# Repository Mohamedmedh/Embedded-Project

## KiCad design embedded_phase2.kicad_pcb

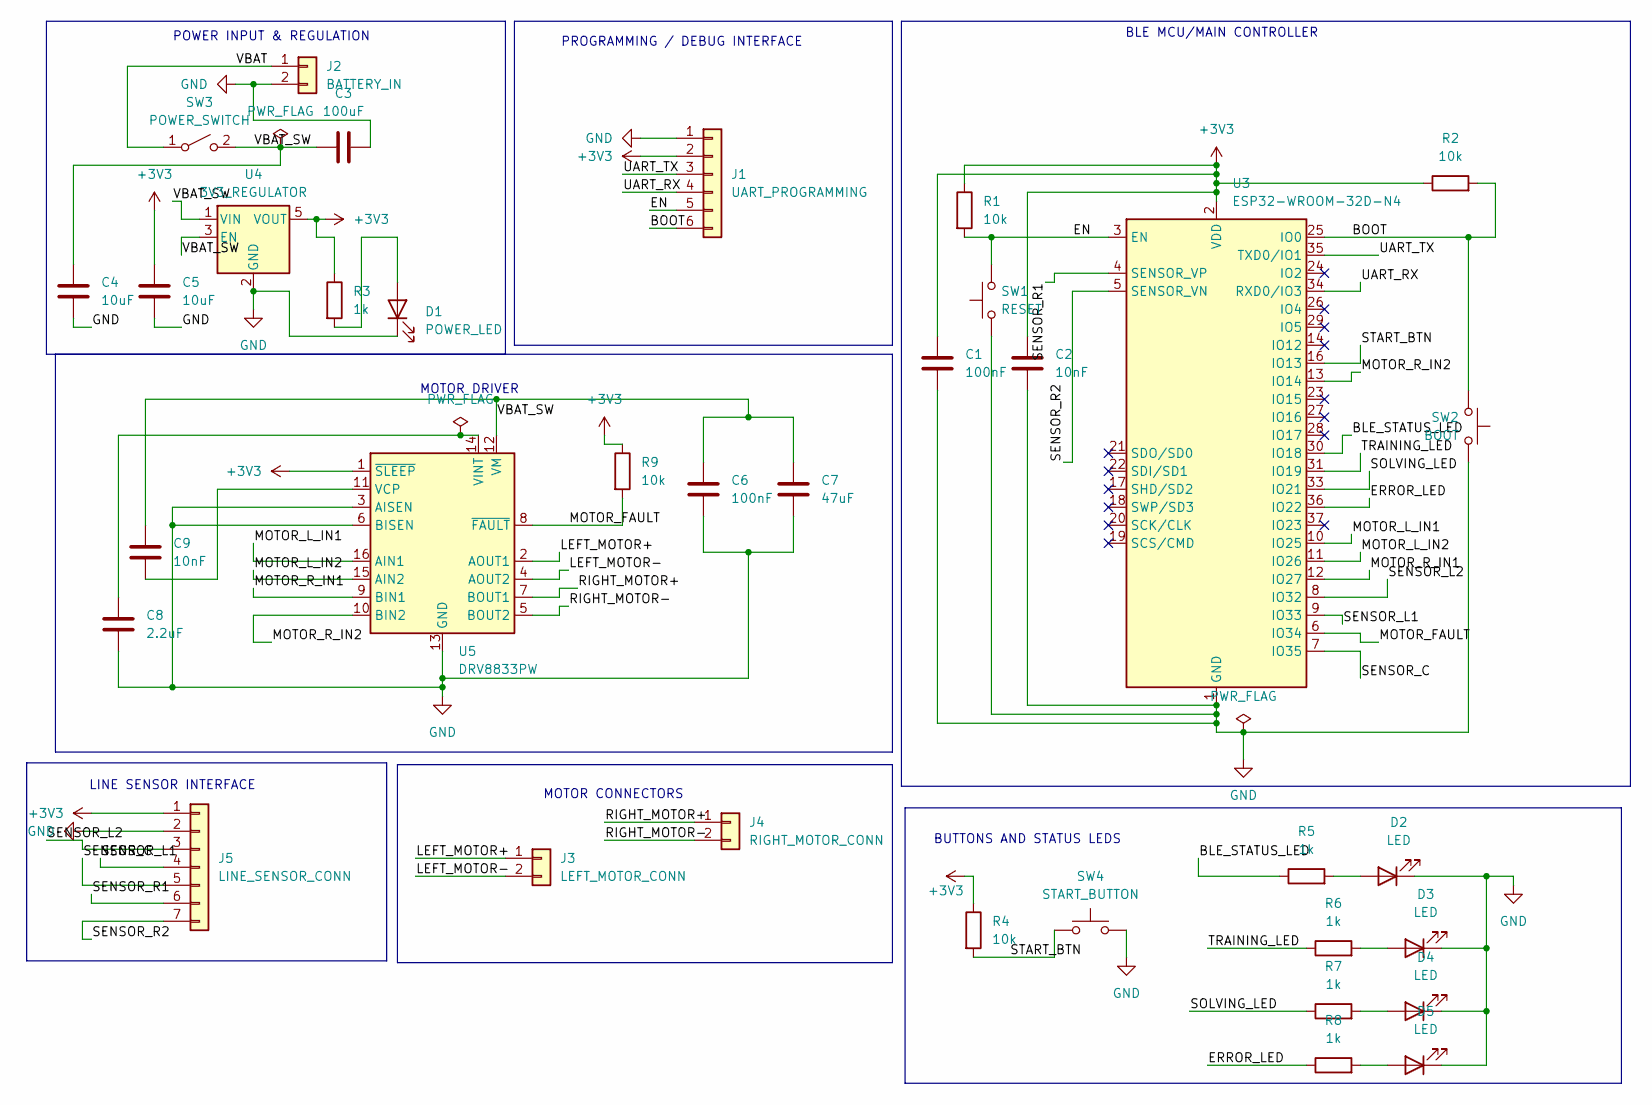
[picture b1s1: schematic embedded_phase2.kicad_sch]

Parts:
C1, C6: 100nF; C_0805_2012Metric
C2, C9: 10nF; C_0805_2012Metric
C3: 100uF; C_1206_3216Metric
C4, C5: 10uF; C_0805_2012Metric
C7: 47uF; C_1206_3216Metric
C8: 2.2uF; C_0805_2012Metric
D1: POWER_LED; LED_0805_2012Metric
D2, D3, D4, D5: LED; LED_0805_2012Metric
J1: UART_PROGRAMMING; PinHeader_1x06_P2.54mm_Vertical_SMD_Pin1Left
J2: BATTERY_IN; PinHeader_1x02_P2.54mm_Vertical_SMD_Pin1Left
J3: LEFT_MOTOR_CONN; PinHeader_1x02_P2.54mm_Vertical_SMD_Pin1Left
J4: RIGHT_MOTOR_CONN; PinHeader_1x02_P2.54mm_Vertical_SMD_Pin1Left
J5: LINE_SENSOR_CONN; PinHeader_1x07_P2.54mm_Vertical_SMD_Pin1Left
R1, R2, R4, R9: 10k; R_0805_2012Metric
R3, R5, R6, R7, R8: 1k; R_0805_2012Metric
SW1: RESET; SW_SPST_TL3342
SW2: BOOT; SW_SPST_TL3342
SW3: POWER_SWITCH; SW_SPST_TL3342
SW4: START_BUTTON; SW_SPST_TL3342
U3: ESP32-WROOM-32D-N4; ESP32-WROOM-32D; MPN ESP32-WR00M-32D-N4; LCSC C473012
U4: 3V3_REGULATOR; SOT-23-5
U5: DRV8833PW; TSSOP-16_4.4x5mm_P0.65mm

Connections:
+3V3: C1.1, C2.1, C5.1, J1.2, J5.1, R1.1, R2.1, R3.1, R4.1, R9.1, U3.2 (VDD), U4.5 (VOUT), U5.1 (~SLEEP)
/BLE_STATUS_LED: R5.1, U3.30 (IO18)
/BOOT: J1.6, R2.2, SW2.2, U3.25 (IO0)
/EN: J1.5, R1.2, SW1.2, U3.3 (EN)
/ERROR_LED: R8.1, U3.36 (IO22)
/LEFT_MOTOR+: J3.1, U5.2 (AOUT1)
/LEFT_MOTOR-: J3.2, U5.4 (AOUT2)
/MOTOR_FAULT: R9.2, U3.6 (IO34), U5.8 (~FAULT)
/MOTOR_L_IN1: U3.10 (IO25), U5.16 (AIN1)
/MOTOR_L_IN2: U3.11 (IO26), U5.15 (AIN2)
/MOTOR_R_IN1: U3.12 (IO27), U5.9 (BIN1)
/MOTOR_R_IN2: U3.13 (IO14), U5.10 (BIN2)
/RIGHT_MOTOR+: J4.1, U5.7 (BOUT1)
/RIGHT_MOTOR-: J4.2, U5.5 (BOUT2)
/SENSOR_C: J5.5, U3.7 (IO35)
/SENSOR_L1: J5.4, U3.9 (IO33)
/SENSOR_L2: J5.3, U3.8 (IO32)
/SENSOR_R1: J5.6, U3.4 (SENSOR_VP)
/SENSOR_R2: J5.7, U3.5 (SENSOR_VN)
/SOLVING_LED: R7.1, U3.33 (IO21)
/START_BTN: R4.2, SW4.1, U3.16 (IO13)
/TRAINING_LED: R6.1, U3.31 (IO19)
/UART_RX: J1.4, U3.34 (RXD0/IO3)
/UART_TX: J1.3, U3.35 (TXD0/IO1)
/VBAT: J2.1, SW3.1 (A)
/VBAT_SW: C3.1, C4.1, C6.1, C7.1, C9.1, SW3.2 (B), U4.1 (VIN), U4.3 (EN), U5.12 (VM)
GND: C1.2, C2.2, C3.2, C4.2, C5.2, C6.2, C7.2, C8.2, D1.1 (K), D2.1 (K), D3.1 (K), D4.1 (K), D5.1 (K), J1.1, J2.2, J5.2, SW1.1, SW2.1, SW4.2, U3.1 (GND), U3.15 (GND), U3.38 (GND), U3.39 (GND), U4.2 (GND), U5.3 (AISEN), U5.6 (BISEN), U5.13 (GND)
unnamed: D1.2 (A), R3.2
unnamed: D2.2 (A), R5.2
unnamed: D3.2 (A), R6.2
unnamed: D4.2 (A), R7.2
unnamed: D5.2 (A), R8.2
unnamed: C9.2, U5.11 (VCP)
unnamed: C8.1, U5.14 (VINT)

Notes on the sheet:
PROGRAMMING / DEBUG INTERFACE
BUTTONS AND STATUS LEDS
POWER INPUT & REGULATION
LINE SENSOR INTERFACE
MOTOR DRIVER
BLE MCU/MAIN CONTROLLER
MOTOR CONNECTORS

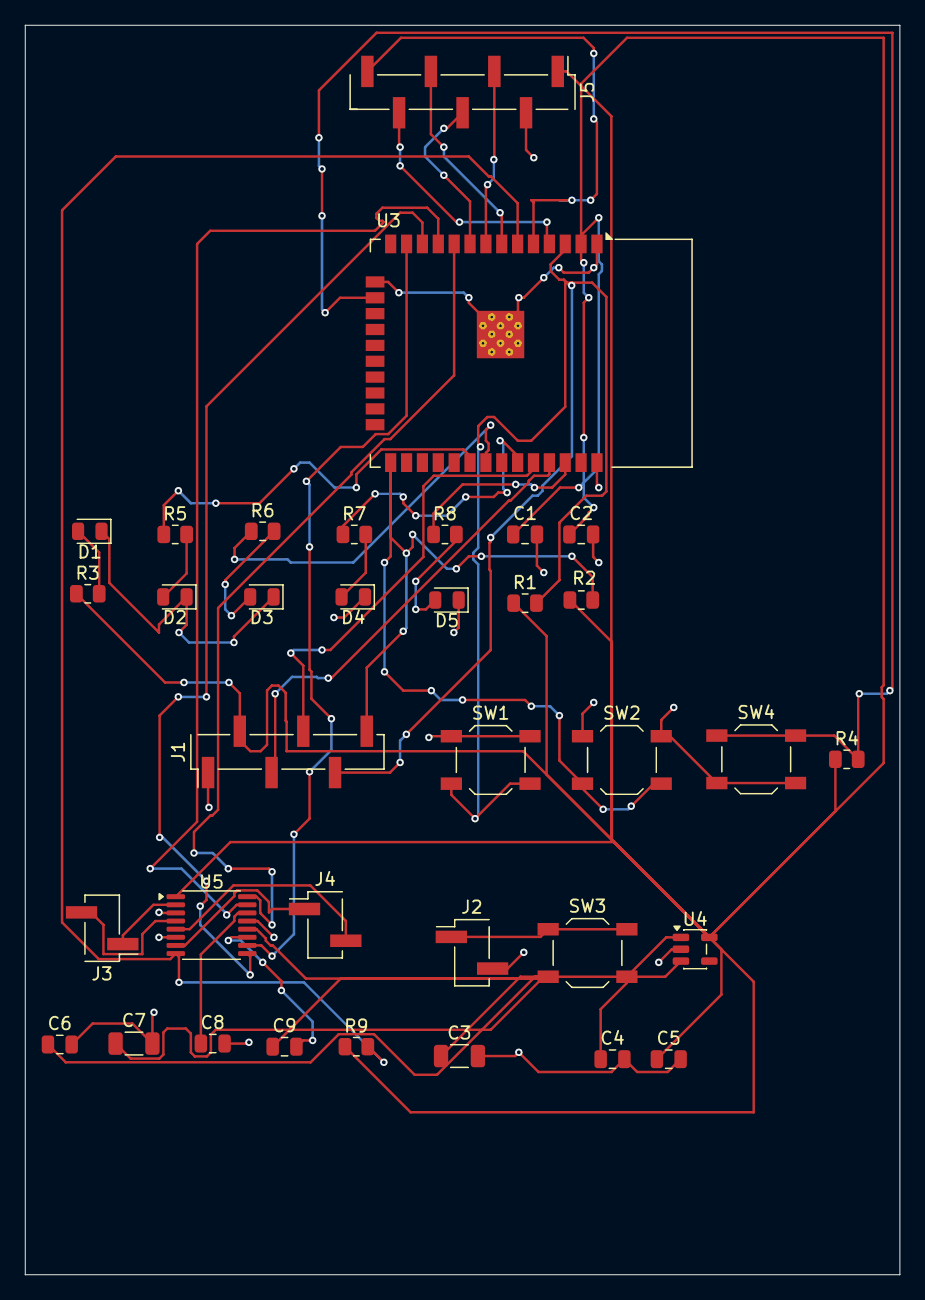
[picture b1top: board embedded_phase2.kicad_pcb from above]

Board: 2 copper layers, 70.0 x 100.0 mm, 35 parts (0 on the bottom side), 34 nets.

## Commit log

2026-04-16 KiCAD Schematic
    Full schematic view for maze follower robot
2026-04-18 Team_Deatails+Contributions.txt
2026-04-18 Contributions+Team_Deatails.txt
2026-04-18 Phase_0_Code.ino
2026-04-18 Rename finalfinal.ino to Phase_1_Arduino.ino
2026-04-18 Rename esp2866_D1_wifi_config.ino to Phase_1_ESP.ino
2026-04-20 Create Python Code
